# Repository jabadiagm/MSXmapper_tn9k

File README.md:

# MSXmapper_tn9k
Mapper de 4 MB para MSX

Mapper de 4MB utilizando uno de los bancos de memoria PSRAM de la tang nano 9k. Compatible con dispositivos con un reloj de hasta 4.8 MHz.

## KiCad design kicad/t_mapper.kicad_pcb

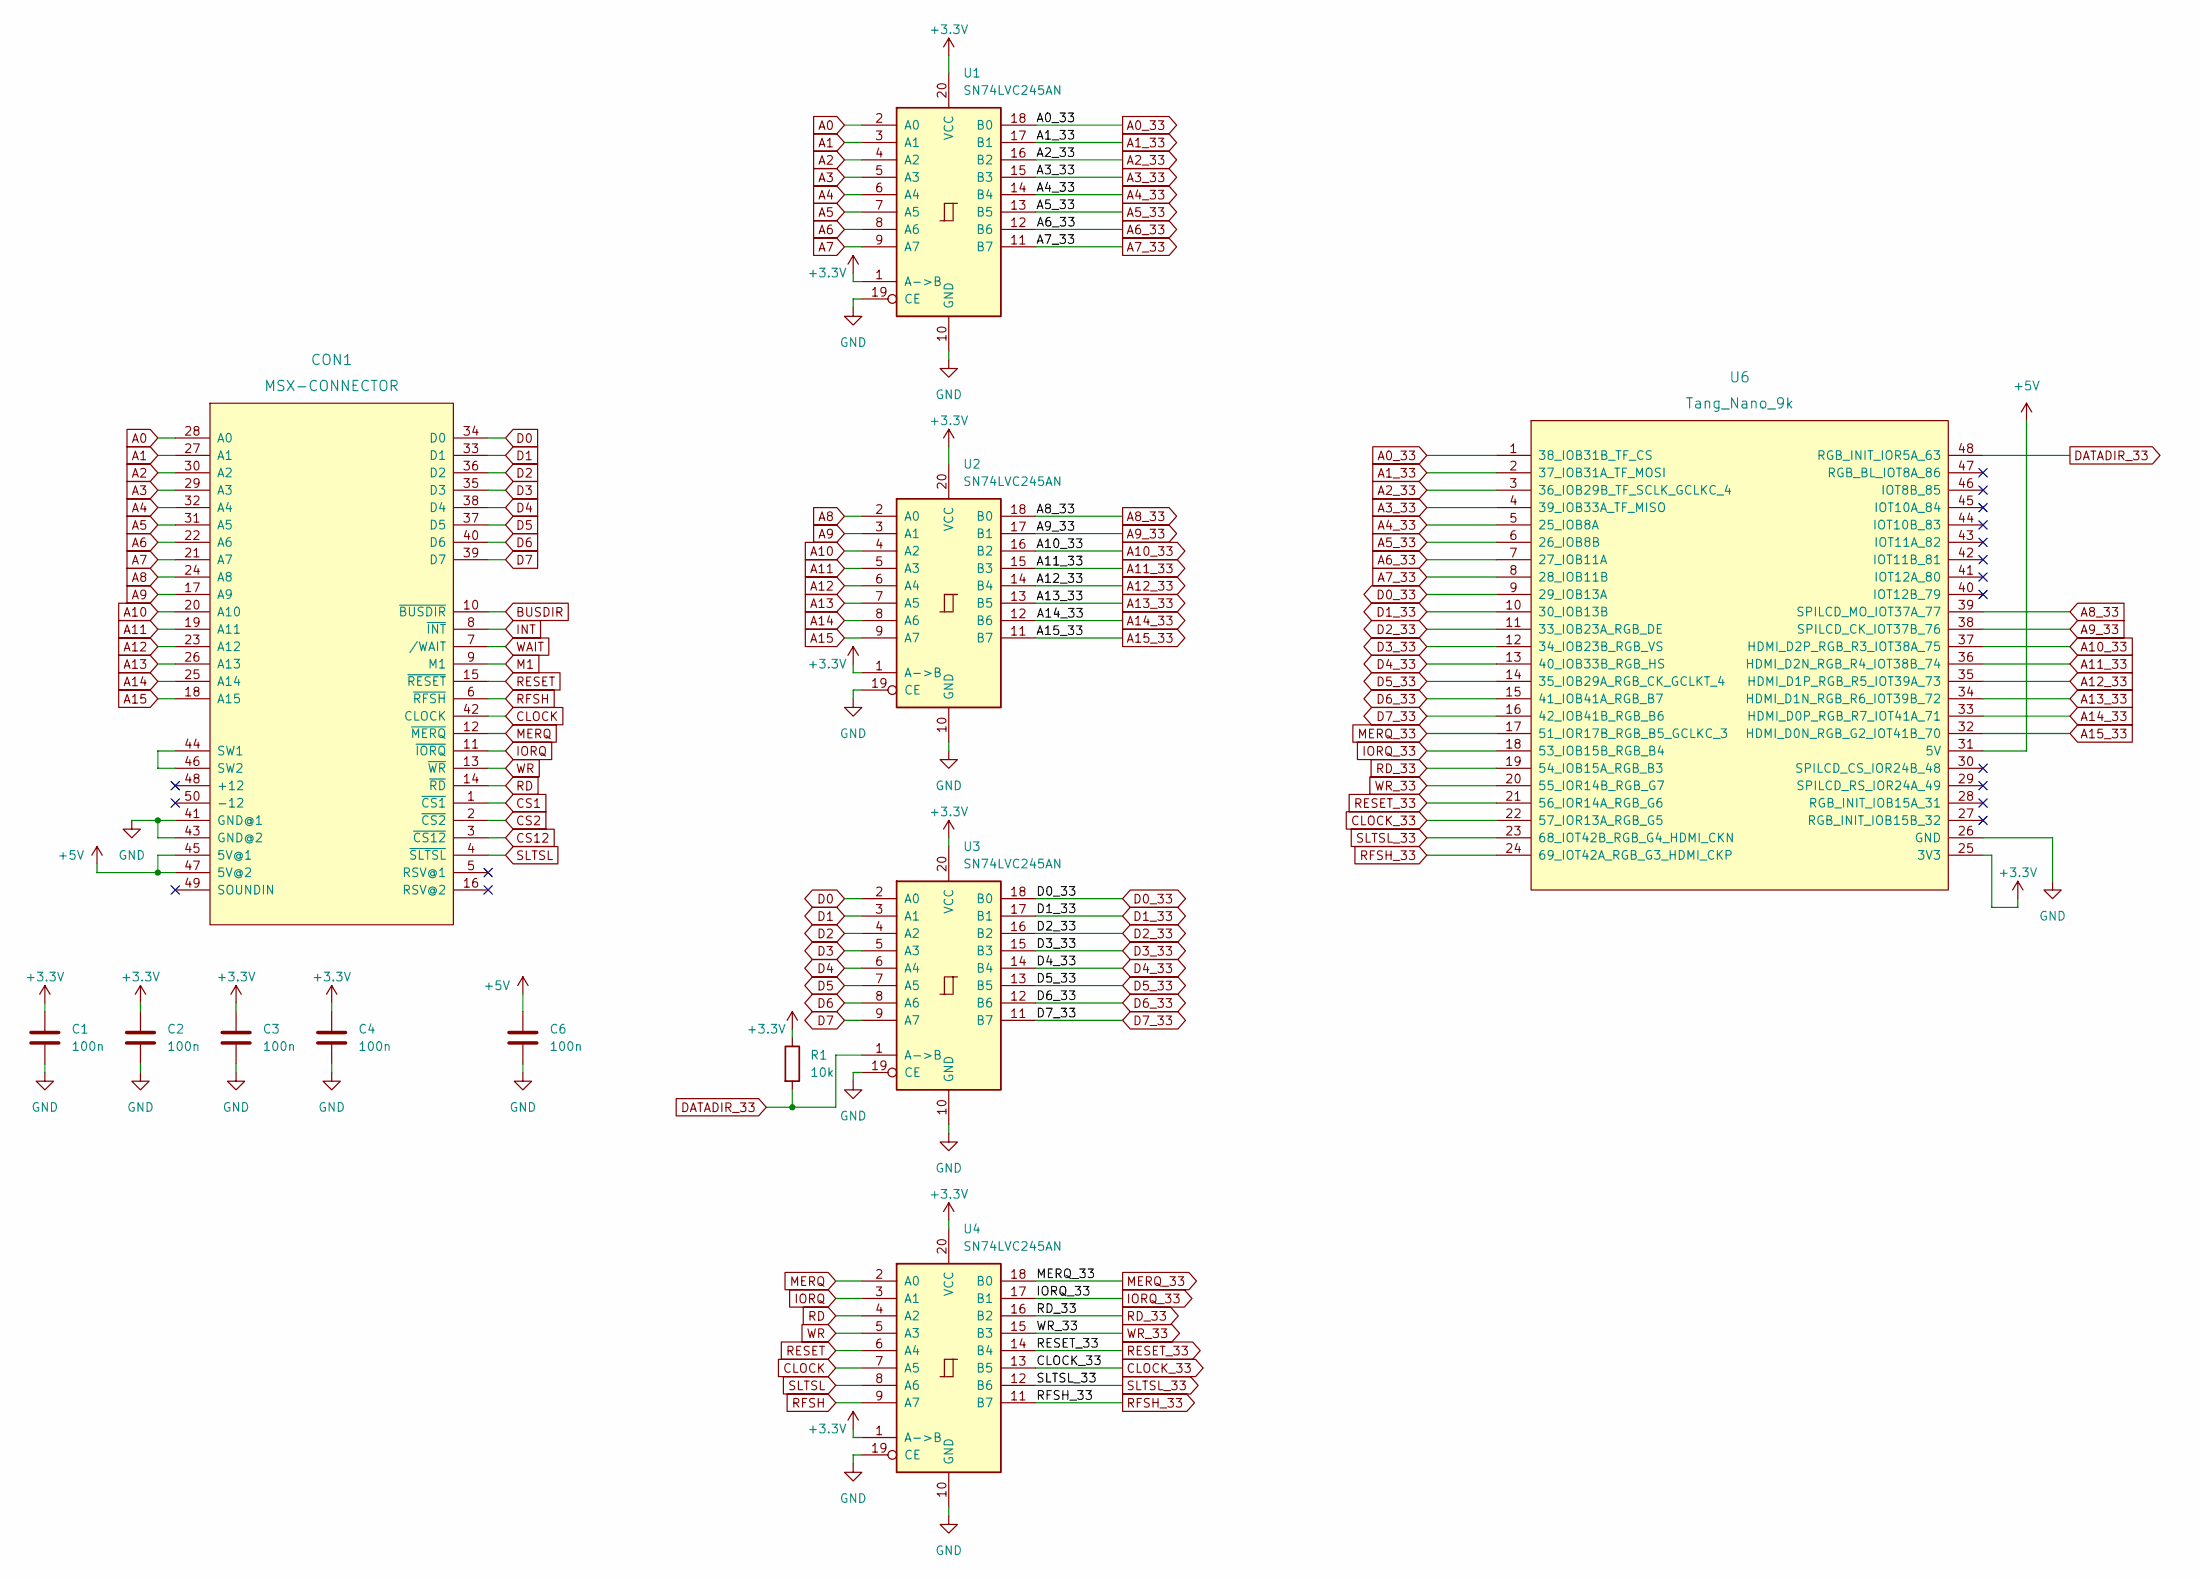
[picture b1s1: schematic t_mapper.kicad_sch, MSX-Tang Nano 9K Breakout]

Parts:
C1, C2, C3, C4, C6: 100n; C_Disc_D4.3mm_W1.9mm_P5.00mm
CON1: MSX-CONNECTOR; CARTRIDGE_MSX
R1: 10k; R_Axial_DIN0207_L6.3mm_D2.5mm_P7.62mm_Horizontal
U1, U2, U3, U4: SN74LVC245AN; DIP-20_W7.62mm_LongPads
U6: Tang_Nano_9k

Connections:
+3.3V: C1.1, C2.1, C3.1, C4.1, R1.1, U1.1 (A->B), U1.20 (VCC), U2.1 (A->B), U2.20 (VCC), U3.20 (VCC), U4.1 (A->B), U4.20 (VCC), U6.25 (3V3)
+5V: C6.1, CON1.45 (5V@1), CON1.47 (5V@2), U6.31 (5V)
A0: CON1.28 (A0), U1.2 (A0)
A0_33: U1.18 (B0), U6.1 (38_IOB31B_TF_CS)
A1: CON1.27 (A1), U1.3 (A1)
A1_33: U1.17 (B1), U6.2 (37_IOB31A_TF_MOSI)
A2: CON1.30 (A2), U1.4 (A2)
A2_33: U1.16 (B2), U6.3 (36_IOB29B_TF_SCLK_GCLKC_4)
A3: CON1.29 (A3), U1.5 (A3)
A3_33: U1.15 (B3), U6.4 (39_IOB33A_TF_MISO)
A4: CON1.32 (A4), U1.6 (A4)
A4_33: U1.14 (B4), U6.5 (25_IOB8A)
A5: CON1.31 (A5), U1.7 (A5)
A5_33: U1.13 (B5), U6.6 (26_IOB8B)
A6: CON1.22 (A6), U1.8 (A6)
A6_33: U1.12 (B6), U6.7 (27_IOB11A)
A7: CON1.21 (A7), U1.9 (A7)
A7_33: U1.11 (B7), U6.8 (28_IOB11B)
A8: CON1.24 (A8), U2.2 (A0)
A8_33: U2.18 (B0), U6.39 (SPILCD_MO_IOT37A_77)
A9: CON1.17 (A9), U2.3 (A1)
A9_33: U2.17 (B1), U6.38 (SPILCD_CK_IOT37B_76)
A10: CON1.20 (A10), U2.4 (A2)
A10_33: U2.16 (B2), U6.37 (HDMI_D2P_RGB_R3_IOT38A_75)
A11: CON1.19 (A11), U2.5 (A3)
A11_33: U2.15 (B3), U6.36 (HDMI_D2N_RGB_R4_IOT38B_74)
A12: CON1.23 (A12), U2.6 (A4)
A12_33: U2.14 (B4), U6.35 (HDMI_D1P_RGB_R5_IOT39A_73)
A13: CON1.26 (A13), U2.7 (A5)
A13_33: U2.13 (B5), U6.34 (HDMI_D1N_RGB_R6_IOT39B_72)
A14: CON1.25 (A14), U2.8 (A6)
A14_33: U2.12 (B6), U6.33 (HDMI_D0P_RGB_R7_IOT41A_71)
A15: CON1.18 (A15), U2.9 (A7)
A15_33: U2.11 (B7), U6.32 (HDMI_D0N_RGB_G2_IOT41B_70)
BUSDIR: CON1.10 (~BUSDIR)
CLOCK: CON1.42 (CLOCK), U4.7 (A5)
CLOCK_33: U4.13 (B5), U6.22 (57_IOR13A_RGB_G5)
CS1: CON1.1 (~CS1)
CS2: CON1.2 (~CS2)
CS12: CON1.3 (~CS12)
D0: CON1.34 (D0), U3.2 (A0)
D0_33: U3.18 (B0), U6.9 (29_IOB13A)
D1: CON1.33 (D1), U3.3 (A1)
D1_33: U3.17 (B1), U6.10 (30_IOB13B)
D2: CON1.36 (D2), U3.4 (A2)
D2_33: U3.16 (B2), U6.11 (33_IOB23A_RGB_DE)
D3: CON1.35 (D3), U3.5 (A3)
D3_33: U3.15 (B3), U6.12 (34_IOB23B_RGB_VS)
D4: CON1.38 (D4), U3.6 (A4)
D4_33: U3.14 (B4), U6.13 (40_IOB33B_RGB_HS)
D5: CON1.37 (D5), U3.7 (A5)
D5_33: U3.13 (B5), U6.14 (35_IOB29A_RGB_CK_GCLKT_4)
D6: CON1.40 (D6), U3.8 (A6)
D6_33: U3.12 (B6), U6.15 (41_IOB41A_RGB_B7)
D7: CON1.39 (D7), U3.9 (A7)
D7_33: U3.11 (B7), U6.16 (42_IOB41B_RGB_B6)
DATADIR_33: R1.2, U3.1 (A->B), U6.48 (RGB_INIT_IOR5A_63)
GND: C1.2, C2.2, C3.2, C4.2, C6.2, CON1.41 (GND@1), CON1.43 (GND@2), U1.10 (GND), U1.19 (CE), U2.10 (GND), U2.19 (CE), U3.10 (GND), U3.19 (CE), U4.10 (GND), U4.19 (CE), U6.26 (GND)
INT: CON1.8 (~INT)
IORQ: CON1.11 (~IORQ), U4.3 (A1)
IORQ_33: U4.17 (B1), U6.18 (53_IOB15B_RGB_B4)
M1: CON1.9 (M1)
MERQ: CON1.12 (~MERQ), U4.2 (A0)
MERQ_33: U4.18 (B0), U6.17 (51_IOR17B_RGB_B5_GCLKC_3)
unnamed: CON1.44 (SW1), CON1.46 (SW2)
RD: CON1.14 (~RD), U4.4 (A2)
RD_33: U4.16 (B2), U6.19 (54_IOB15A_RGB_B3)
RESET: CON1.15 (~RESET), U4.6 (A4)
RESET_33: U4.14 (B4), U6.21 (56_IOR14A_RGB_G6)
RFSH: CON1.6 (~RFSH), U4.9 (A7)
RFSH_33: U4.11 (B7), U6.24 (69_IOT42A_RGB_G3_HDMI_CKP)
SLTSL: CON1.4 (~SLTSL), U4.8 (A6)
SLTSL_33: U4.12 (B6), U6.23 (68_IOT42B_RGB_G4_HDMI_CKN)
WAIT: CON1.7 (/WAIT)
WR: CON1.13 (~WR), U4.5 (A3)
WR_33: U4.15 (B3), U6.20 (55_IOR14B_RGB_G7)

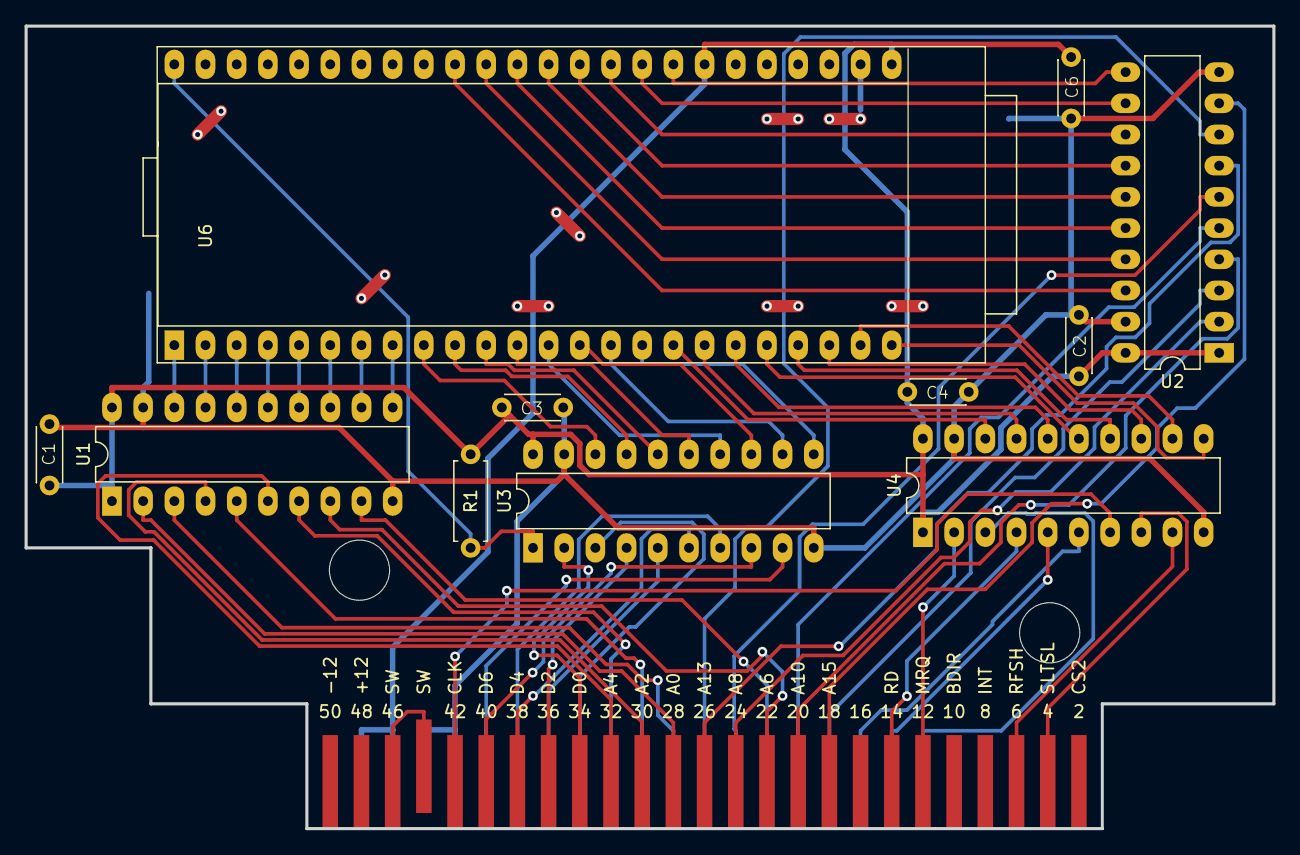
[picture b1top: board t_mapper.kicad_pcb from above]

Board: 2 copper layers, 101.6 x 65.3 mm, 12 parts (0 on the bottom side), 69 nets.

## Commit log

2023-06-25 Inicial
2023-07-15 Reducida frecuencia de trabajo de psram a 72 MHz debido a las nuevas tang nano 9k
2023-07-29 Corregido bug de dirección de bus
    ---------------------------------
    Fixed bug with busdir
2023-09-03 Sincronizada escritura con reloj para gestionar tiempos del t80
    Synchronized write with clock to deal with t80 timing
2023-09-03 Borrados archivos svn
    Deleted svn files
